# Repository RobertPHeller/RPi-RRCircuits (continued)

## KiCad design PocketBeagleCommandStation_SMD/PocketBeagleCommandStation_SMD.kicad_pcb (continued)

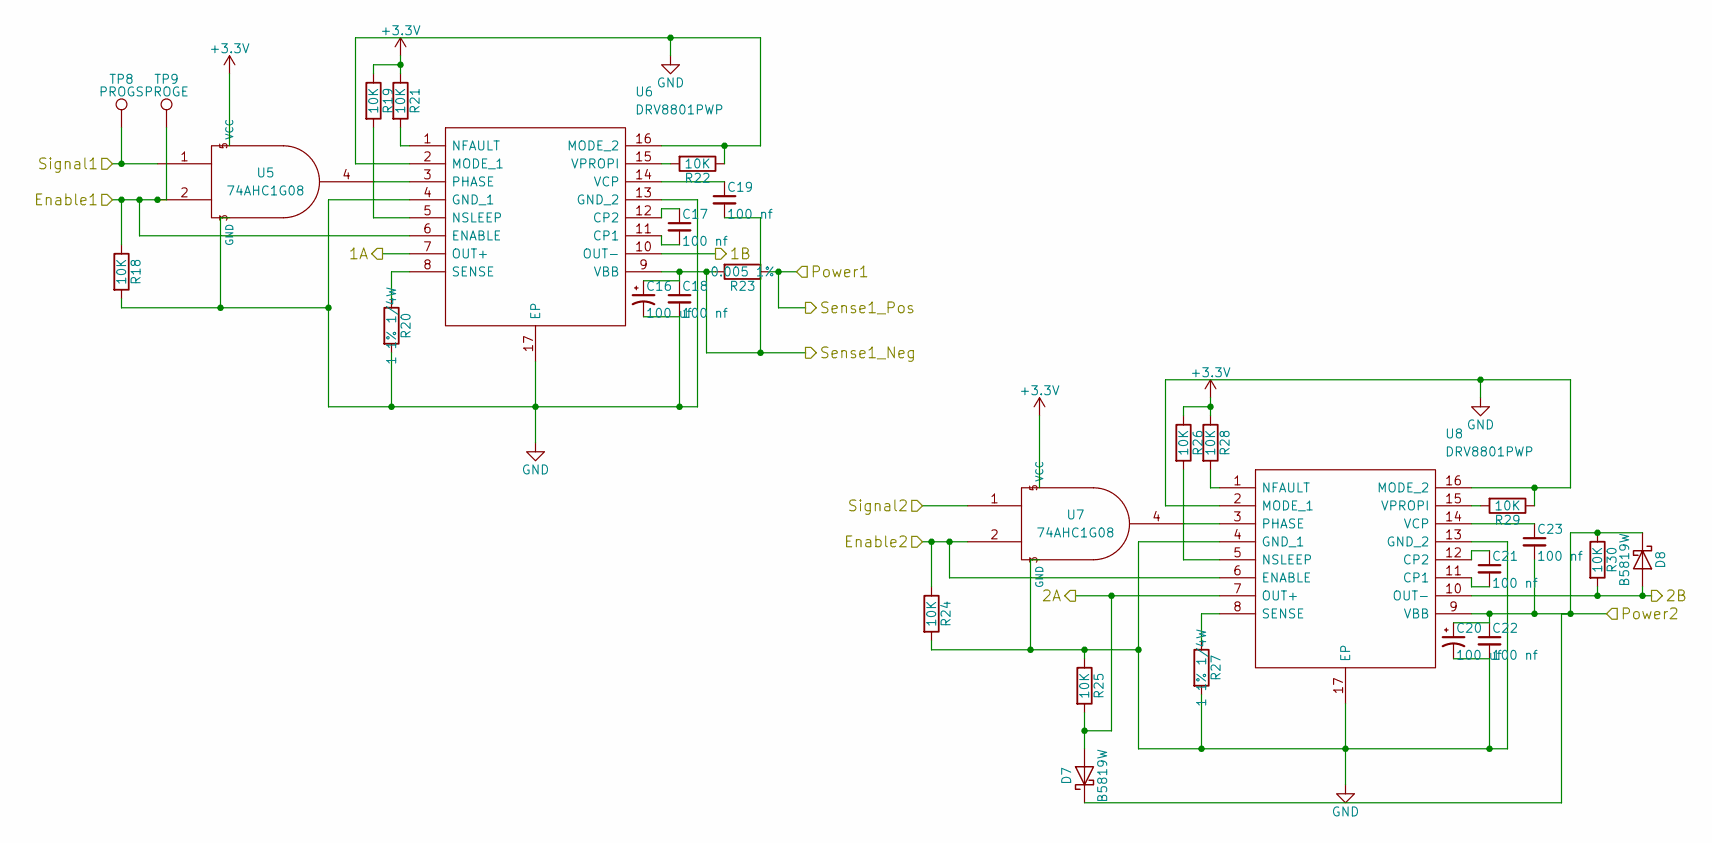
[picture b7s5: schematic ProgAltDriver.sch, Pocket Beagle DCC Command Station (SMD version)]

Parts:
C16, C20: 100 uf; CP_Elec_6.3x7.7; Mouser Part Number 710-865080545012
C17, C18, C19, C21, C22, C23: 100 nf; C_0603; Mouser Part Number 603-CC603KPX7R9BB104
D7, D8: B5819W; D_SOD-323; Mouser Part Number 833-B5819WS-TP
R18, R19, R21, R22, R24, R25, R26, R28, R29, R30: 10K; R_0603; Mouser Part Number 279-CRGCQ0603F10K
R20, R27: 1 1% 1/4W; R_1206; Mouser Part Number 71-CRCW1206-1-E3
R23: 0.005 1%; R_0612; Mouser Part Number 71-WSKW0612L5000FEA
TP8: PROGS; Measurement_Point_Round-SMD-Pad_Small
TP9: PROGE; Measurement_Point_Round-SMD-Pad_Small
U5, U7: 74AHC1G08; SOT-353_SC-70-5; Mouser Part Number 595-SN74AHC1G08DCRE4
U6, U8: DRV8801PWP; SOP65P640X120-17N; Mouser Part Number 595-DRV8801PWP

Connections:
+3V3: R19.1, R21.1, R26.1, R28.1, U5.5 (VCC), U7.5 (VCC); also elsewhere on the board
+12V: C20.1, C22.1, C23.2, D7.1 (K), D8.1 (K), R30.1, U8.9 (VBB); also elsewhere on the board
/OLBC_A: D7.2 (A), R25.2, U8.7 (OUT+); also elsewhere on the board
/OLBC_B: D8.2 (A), R30.2, U8.10 (OUT-); also elsewhere on the board
/OPS-ENABLE: R24.1, U7.2, U8.6 (ENABLE); also elsewhere on the board
/OPS-SIG: U7.1; also elsewhere on the board
/PROG-ENABLE: R18.1, TP9.1, U5.2, U6.6 (ENABLE); also elsewhere on the board
/PROG-SENSE-NEG: C16.1, C18.1, C19.2, R23.2, U6.9 (VBB); also elsewhere on the board
/PROG-SENSE-POS: R23.1; also elsewhere on the board
/PROG-SIG: TP8.1, U5.1; also elsewhere on the board
/Prog and LCC Alt H/L Driver/1A: U6.7 (OUT+); also elsewhere on the board
/Prog and LCC Alt H/L Driver/1B: U6.10 (OUT-); also elsewhere on the board
GND: C16.2, C18.2, C20.2, C22.2, R18.2, R20.2, R22.1, R24.2, R25.1, R27.2, R29.1, U5.3 (GND), U6.2 (MODE_1), U6.4 (GND_1), U6.13 (GND_2), U6.16 (MODE_2), U6.17 (EP), U7.3 (GND), U8.2 (MODE_1), U8.4 (GND_1), U8.13 (GND_2), U8.16 (MODE_2), U8.17 (EP); also elsewhere on the board
unnamed: C17.1, U6.12 (CP2)
unnamed: C17.2, U6.11 (CP1)
unnamed: C19.1, U6.14 (VCP)
unnamed: C21.1, U8.12 (CP2)
unnamed: C21.2, U8.11 (CP1)
unnamed: C23.1, U8.14 (VCP)
unnamed: R19.2, U6.5 (NSLEEP)
unnamed: R20.1, U6.8 (SENSE)
unnamed: R21.2, U6.1 (NFAULT)
unnamed: R22.2, U6.15 (VPROPI)
unnamed: R26.2, U8.5 (NSLEEP)
unnamed: R27.1, U8.8 (SENSE)
unnamed: R28.2, U8.1 (NFAULT)
unnamed: R29.2, U8.15 (VPROPI)
unnamed: U5.4, U6.3 (PHASE)
unnamed: U7.4, U8.3 (PHASE)

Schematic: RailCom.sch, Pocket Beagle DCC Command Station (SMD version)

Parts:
C24, C25, C26: 33 pf; C_0603; Mouser Part Number 187-CL10C330JB8NNNC
D10: B5819W; D_SOD-323; Mouser Part Number 833-B5819WS-TP
Q4, Q12: DMNH6022SSDQ; SOIC-8_3.9x4.9mm_Pitch1.27mm; Mouser Part Number 621-DMNH6022SSDQ-13
Q5, Q7, Q9, Q10: 2N7002; SOT-23; Mouser Part Number 512-2N7002
Q6, Q8, Q13, Q14: DTC143T; SOT-323_SC-70; Mouser Part Number 863-NSBC143TPDXV6T1G
R32, R34, R35, R36, R45: 10K; R_0603; Mouser Part Number 279-CRGCQ0603F10K
R33, R37: 2.4; R_1206; Mouser Part Number 71-CRCW12062R40FKEA
R38: 1.5K 1/4W; R_1206; Mouser Part Number 71-CRCW12061K50FKEAC
R39: 10K 1/4W; R_1206; Mouser Part Number 279-CRGCQ1206F10K
R40, R41, R42: 2.4K; R_0603; Mouser Part Number 667-ERJ-3EKF2401V
R43, R44, R46, R47: 24.9; R_1206; Mouser Part Number 652-CRT1206DY24R9ELF
U10: LMV339; TSSOP-14_4.4x5mm_Pitch0.65mm; Mouser Part Number 511-LMV339IPT

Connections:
+3V3: R34.1, R35.2, R41.1, R42.1, U10.3 (V+), U10.10 (-); also elsewhere on the board
/DCC_VS: R38.1, R39.1; also elsewhere on the board
/OLBC_A: Q12.7, Q12.8 (D); also elsewhere on the board
/OLBC_B: Q12.5 (D), Q12.6; also elsewhere on the board
/OPS_A: Q4.7, Q4.8 (D); also elsewhere on the board
/OPS_B: Q4.5 (D), Q4.6; also elsewhere on the board
/RAILCOM-DATA: D10.2 (A), R41.2, U10.2, U10.14; also elsewhere on the board
/RAILCOM-DIR: D10.1 (K), R42.2, U10.1; also elsewhere on the board
/RAILCOM-ENABLE: Q10.1 (G), R40.1; also elsewhere on the board
/RAILCOM-SHORT: Q6.3 (C), Q7.1 (G), Q8.3 (C), Q13.3 (C), Q14.3 (C), R35.1; also elsewhere on the board
/RAILCOM_OLBC_VREF: U10.9 (+); also elsewhere on the board
/RAILCOM_VREF: U10.5 (+), U10.7 (+); also elsewhere on the board
/Railcomm Interface/GATE-EN: Q4.2 (G), Q4.4 (G), Q5.3 (D), Q9.3 (D), Q12.2 (G), Q12.4 (G), R38.2
GND: C24.2, C25.2, C26.2, Q5.2 (S), Q6.2 (E), Q7.2 (S), Q8.2 (E), Q9.2 (S), Q10.2 (S), Q13.2 (E), Q14.2 (E), R33.1, R37.2, R40.2, R44.1, R46.2, U10.11 (+), U10.12 (V-); also elsewhere on the board
unnamed: C24.1, R32.1, U10.4 (-)
unnamed: C25.1, R36.1, U10.6 (-)
unnamed: C26.1, R45.1, U10.8 (-)
unnamed: Q4.1 (S), Q6.1 (B), R32.2, R33.2
unnamed: Q4.3 (S), Q8.1 (B), R36.2, R37.1
unnamed: Q5.1 (G), Q7.3 (D), R34.2
unnamed: Q9.1 (G), Q10.3 (D), R39.2
unnamed: Q12.1 (S), R43.2, R45.2
unnamed: Q12.3 (S), R47.1
unnamed: Q13.1 (B), R43.1, R44.2
unnamed: Q14.1 (B), R46.1, R47.2

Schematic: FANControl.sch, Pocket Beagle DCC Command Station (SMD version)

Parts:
C34: 100 uf; C_0603; Mouser Part Number 603-CC603KPX7R9BB104
D9: 1SS352H3F; D_SOD-323; Mouser Part Number 757-1SS352H3F
J6: - Fan +; TerminalBlock_Pheonix_MPT-2.54mm_2pol; Mouser Part Number 651-1725656
M1: Fan_IEC60617; 25mmFanMount; Mouser Part Number 490-CFM2510B1100-218
Q3: BSP52T3G; SOT-223; Mouser Part Number 863-BSP52T3G
R31: 1K; R_0603; Mouser Part Number 279-CRGCQ0603F1K0
U9: MCP9700T-E_LT; SOT65P210X110-5N; Mouser Part Number 579-MCP9700T-E/LT

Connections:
+3V3: C34.1, U9.4 (VDD); also elsewhere on the board
+12V: J6.1; also elsewhere on the board
/FAN-CONTROL: R31.2; also elsewhere on the board
/TEMP-SENSE: U9.3 (VOUT); also elsewhere on the board
GND: C34.2, D9.2 (A), Q3.3 (E), U9.2 (GND); also elsewhere on the board
unnamed: D9.1 (K), J6.2, Q3.2 (C), Q3.4 (C2)
unnamed: Q3.1 (B), R31.1

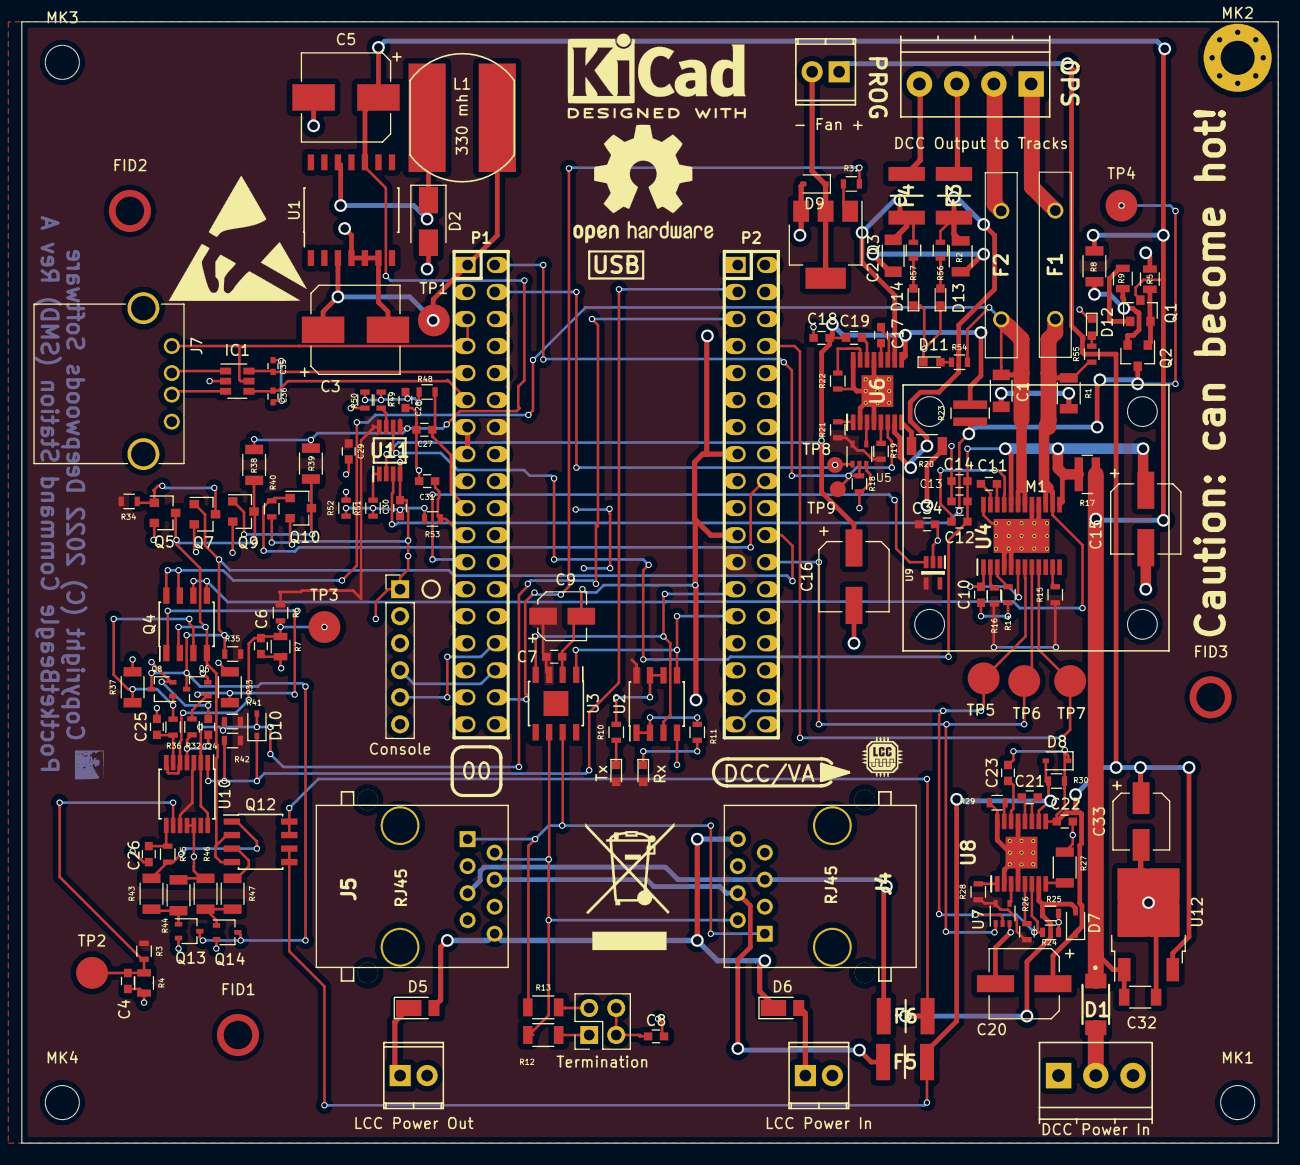
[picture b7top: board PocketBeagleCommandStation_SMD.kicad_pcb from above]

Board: 2 copper layers, 118.1 x 105.4 mm, 169 parts (0 on the bottom side), 108 nets.

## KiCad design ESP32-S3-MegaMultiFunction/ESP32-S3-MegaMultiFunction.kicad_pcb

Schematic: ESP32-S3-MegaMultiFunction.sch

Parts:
FD101, FD102, FD103: Fiduial; Fiducial_Modern_SilkscreenTop
J101: Conn_02x05_Odd_Even; IDC_Header_Straight_10pins
MK101, MK102, MK103, MK104: Mounting_Hole; MountingHole_3.5mm

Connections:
/Line1: J101.10; also elsewhere on the board
/Line2: J101.9; also elsewhere on the board
/Line3: J101.8; also elsewhere on the board
/Line4: J101.7; also elsewhere on the board
/Line5: J101.4; also elsewhere on the board
/Line6: J101.3; also elsewhere on the board
/Line7: J101.2; also elsewhere on the board
/Line8: J101.1; also elsewhere on the board
GND: J101.5; also elsewhere on the board

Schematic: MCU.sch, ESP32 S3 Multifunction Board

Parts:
C201, C202: 10uf; C_0805; Mouser Part Number 187-CL21A106MQFNNNE
C203, C208, C210, C217: 1uf; C_0402; Mouser Part Number 80-C0402C101K8RAUTO
C204, C205, C206, C207, C211, C212: 100nf; C_0402; Mouser Part Number 710-885012105001
C209: 100pf; C_0402; Mouser Part Number 80-C0402C101K3RAUTO
C213, C214, C215, C216: 22pf; C_0402; Mouser Part Number 187-CL05C220JB5NNND
D201: ACT1; LED_0402; Mouser Part Number 710-150040GS73220
D202: ACT2; LED_0402; Mouser Part Number 710-150040SS73220
IC201: ESP32-S3FN8; QFN-56-1EP_7x7mm_Pitch0.4mm; Manufacturer_Part_Number ESP32-S3FN8; Mouser Part Number 356-ESP32-S3FN8
IC202: USBLC6-2SC6; SOT-23-6; Mouser Part Number 511-USBLC6-2SC6
J201: USB_OTG; GCT_USB4105-GF-A; Mouser Part Number 640-USB4105-GF-A-120
L201: 2.0nH; L_0402; Mouser Part Number 810-MLG1005S2N0ST000
R201, R202, R203, R204, R210, R211: 10K; R_0402; Mouser Part Number 603-RC0402JR-1310KL
R205, R207: 2.4K; R_0402; Mouser Part Number 71-CRCW06032K40JNEAC
R206, R208: 270; R_0402; Mouser Part Number 754-RR0510P-271D
R209: 0; R_0402; Mouser Part Number 71-CRCW04020000Z0EDC
R212, R213: 5.1K; R_0402
SW201: RESET; SW_SPST_B3U-1000P-B; Mouser Part Number 653-B3U-1000P-B
SW202: BOOT; SW_SPST_B3U-1000P-B; Mouser Part Number 653-B3U-1000P-B
U201, U202, U203: MCP23017; SOIC-28W_7.5x17.9mm_Pitch1.27mm
Y201: 40 Mhz; FA20_H; Mouser Part Number 732-FA-20H40MF10Z-W3

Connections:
/Buttons/Button1: U203.21 (GPA0); also elsewhere on the board
/Buttons/Button2: U203.22 (GPA1); also elsewhere on the board
/Buttons/Button3: U203.23 (GPA2); also elsewhere on the board
/Buttons/Button4: U203.24 (GPA3); also elsewhere on the board
/Buttons/Button5: U203.25 (GPA4); also elsewhere on the board
/Buttons/Button6: U203.26 (GPA5); also elsewhere on the board
/Buttons/Button7: U203.27 (GPA6); also elsewhere on the board
/Buttons/Button8: U203.28 (GPA7); also elsewhere on the board
/CAN Transciver/CAN_RX: IC201.9 (GPIO4); also elsewhere on the board
/CAN Transciver/CAN_TX: IC201.10 (GPIO5); also elsewhere on the board
/LED/Drivers/LED1: U201.1 (GPB0); also elsewhere on the board
/LED/Drivers/LED2: U201.2 (GPB1); also elsewhere on the board
/LED/Drivers/LED3: U201.3 (GPB2); also elsewhere on the board
/LED/Drivers/LED4: U201.4 (GPB3); also elsewhere on the board
/LED/Drivers/LED5: U201.5 (GPB4); also elsewhere on the board
/LED/Drivers/LED6: U201.6 (GPB5); also elsewhere on the board
/LED/Drivers/LED7: U201.7 (GPB6); also elsewhere on the board
/LED/Drivers/LED8: U201.8 (GPB7); also elsewhere on the board
/Line1: U203.1 (GPB0); also elsewhere on the board
/Line2: U203.2 (GPB1); also elsewhere on the board
/Line3: U203.3 (GPB2); also elsewhere on the board
/Line4: U203.4 (GPB3); also elsewhere on the board
/Line5: U203.5 (GPB4); also elsewhere on the board
/Line6: U203.6 (GPB5); also elsewhere on the board
/Line7: U203.7 (GPB6); also elsewhere on the board
/Line8: U203.8 (GPB7); also elsewhere on the board
/MCU/D+: C216.1, IC201.26 (GPIO20), IC202.1 (I/O1_1)
/MCU/D-: C215.2, IC201.25 (GPIO19), IC202.3 (I/O2_1)
/MCU/GPIO0(Act2): D202.1 (K), IC201.5 (GPIO0), SW202.2
/MCU/GPIO15(Act1): D201.1 (K), IC201.21 (XTAL_32K_P)
/MCU/Motor1: U202.21 (GPA0); also elsewhere on the board
/MCU/Motor2: U202.22 (GPA1); also elsewhere on the board
/MCU/Motor3: U202.23 (GPA2); also elsewhere on the board
/MCU/Motor4: U202.24 (GPA3); also elsewhere on the board
/MCU/Motor5: U202.25 (GPA4); also elsewhere on the board
/MCU/Motor6: U202.26 (GPA5); also elsewhere on the board
/MCU/Motor7: U202.27 (GPA6); also elsewhere on the board
/MCU/Motor8: U202.28 (GPA7); also elsewhere on the board
/MCU/OD1: U201.21 (GPA0); also elsewhere on the board
/MCU/OD2: U201.22 (GPA1); also elsewhere on the board
/MCU/OD3: U201.23 (GPA2); also elsewhere on the board
/MCU/OD4: U201.24 (GPA3); also elsewhere on the board
/MCU/OD5: U201.25 (GPA4); also elsewhere on the board
/MCU/OD6: U201.26 (GPA5); also elsewhere on the board
/MCU/OD7: U201.27 (GPA6); also elsewhere on the board
/MCU/OD8: U201.28 (GPA7); also elsewhere on the board
/MCU/Points1: U202.1 (GPB0); also elsewhere on the board
/MCU/Points2: U202.2 (GPB1); also elsewhere on the board
/MCU/Points3: U202.3 (GPB2); also elsewhere on the board
/MCU/Points4: U202.4 (GPB3); also elsewhere on the board
/MCU/Points5: U202.5 (GPB4); also elsewhere on the board
/MCU/Points6: U202.6 (GPB5); also elsewhere on the board
/MCU/Points7: U202.7 (GPB6); also elsewhere on the board
/MCU/Points8: U202.8 (GPB7); also elsewhere on the board
/MCU/RESET: C210.1, IC201.4 (CHIP_PU), R204.2, SW201.2
/MCU/SCL: IC201.8 (GPIO3), R205.1, U201.12 (SCL), U202.12 (SCL), U203.12 (SCL); also elsewhere on the board
/MCU/SDA: IC201.7 (GPIO2), R207.2, U201.13 (SDA), U202.13 (SDA), U203.13 (SDA); also elsewhere on the board
/MCU/VDD3P3: C201.1, C202.1, C203.1, C205.1, IC201.2 (VDD3P3_1), IC201.3 (VDD3P3_2), L201.2
GND: C201.2, C202.2, C203.2, C204.2, C205.2, C206.2, C207.2, C208.2, C209.2, C210.2, C211.2, C212.2, C213.1, C214.1, C215.1, C216.2, C217.2, IC201.57 (EP), IC202.2 (GND), J201.A1/B (GND), J201.B1/A (GND), J201.G1 (SHIELD), J201.G2 (SHIELD), J201.G3 (SHIELD), J201.G4 (SHIELD), R212.2, R213.2, SW201.1, SW202.1, U201.10 (GND), U201.16 (A1), U201.17 (A2), U202.10 (GND), U202.15 (A0), U202.16 (A1), U202.17 (A2), U203.10 (GND), U203.15 (A0), U203.17 (A2), Y201.2, Y201.4; also elsewhere on the board
unnamed: C213.2, R209.1, Y201.3
unnamed: C214.2, IC201.53 (XTAL_N), Y201.1
unnamed: C217.1, IC201.29 (VDD_SPI)
unnamed: D201.2 (A), R206.2
unnamed: D202.2 (A), R208.2
unnamed: IC201.54 (XTAL_P), R209.2
unnamed: IC202.4 (I/O2_2), J201.A7 (D-), J201.B7 (D-)
unnamed: IC202.6 (I/O1_2), J201.A6 (D+), J201.B6 (D+)
unnamed: J201.A5 (CC1), R213.1
unnamed: J201.B5 (CC2), R212.1
unnamed: R201.2, U201.18 (~RESET)
unnamed: R202.2, U201.15 (A0)
unnamed: R203.2, U202.18 (~RESET)
unnamed: R210.2, U203.18 (~RESET)
unnamed: R211.2, U203.16 (A1)
VBUS: IC202.5 (VBUS), J201.A4/B (VBUS), J201.B4/A (VBUS); also elsewhere on the board

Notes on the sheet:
Pins 2,3
Pin 46
Pins 55, 56
Pin 20
One for each MCP23017

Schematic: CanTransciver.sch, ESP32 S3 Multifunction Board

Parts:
C301: .1 uf; C_0603; Mouser Part Number 710-885012206095
C302: 15 uf 15V; CP_Elec_4x5.7; Mouser Part Number 647-UUD1C150MCL
C303: 47 nf; C_0603; Mouser Part Number 710-885012206093
D301, D302: DFLS240-7; D_PowerDI-123; Mouser Part Number 621-DFLS240-7
J301, J302: RJ45; RJ45_8N-S; Mouser Part Number 710-615008144221
JP301: Termination; Pin_Header_Straight_2x02_Pitch2.54mm; Mouser Part Number 649-67997-404HLF
R301, R302: 60 Ohms; R_1206; Mouser Part Number 71-CRCW120660R0KNAIF
T301: - 15 in +; TerminalBlock_Pheonix_MPT-2.54mm_2pol; Mouser Part Number 651-1725656
T302: - 15 out +; TerminalBlock_Pheonix_MPT-2.54mm_2pol; Mouser Part Number 651-1725656
U301: TCAN332DR; SOIC-8_3.9x4.9mm_Pitch1.27mm; Mouser Part Number 595-TCAN332DR

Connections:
/CAN Transciver/CANH: J301.1, J302.1, R301.1, U301.7 (CANH)
/CAN Transciver/CANL: J301.2, J302.2, R302.1, U301.6 (CANL)
/CAN Transciver/CAN_RX: U301.4 (R); also elsewhere on the board
/CAN Transciver/CAN_TX: U301.1 (D); also elsewhere on the board
CAN +12V: D301.1 (K), D302.2 (A), J301.8, J302.8; also elsewhere on the board
GND: C301.2, C302.2, C303.2, J301.3, J301.6, J301.7, J302.3, J302.6, J302.7, T301.2, T302.2, U301.2 (GND); also elsewhere on the board
unnamed: C303.1, JP301.3, JP301.4
unnamed: D301.2 (A), T301.1
unnamed: D302.1 (K), T302.1
unnamed: J301.4, J302.4
unnamed: J301.5, J302.5
unnamed: JP301.1, R301.2
unnamed: JP301.2, R302.2

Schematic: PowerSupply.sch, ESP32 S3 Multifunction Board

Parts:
C401: 220 uf 25V; CP_Elec_8x10; Mouser Part Number 647-UWT1E221MNL1GS
C402: 22 uf 100V; CP_Elec_8x10; Mouser Part Number 647-UUX2A220MNL6GS
D401: CMSH1-60 TR13; D_SMB; Mouser Part Number 610-CMSH1-60TR13
D402, D403: DFLS240-7; D_PowerDI-123; Mouser Part Number 621-DFLS240-7
L401: 330 uh; SRN1060; Mouser Part Number 652-SRN1060-331M
U401: LM2574N-3.3; SOIC-14_7.4x8.7mm_Pitch1.27mm; Mouser Part Number 926-LM2574MX33NOPB

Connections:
CAN +12V: D402.2 (A); also elsewhere on the board
GND: C401.2, C402.2, D401.2 (A), U401.4 (SigGnd), U401.5 (Oh/Off), U401.6 (PwrGnd); also elsewhere on the board
unnamed: C402.1, D402.1 (K), D403.1 (K), U401.10 (Vin)
unnamed: D401.1 (K), L401.1, U401.12 (Out)
VBUS: D403.2 (A); also elsewhere on the board

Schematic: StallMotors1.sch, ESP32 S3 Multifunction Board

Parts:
C501, C502: .1 uf; C_0603; Mouser Part Number 710-885012206095
D501: DFLS240-7; D_PowerDI-123; Mouser Part Number 621-DFLS240-7
J501: -SM+; TerminalBlock_Pheonix_MPT-2.54mm_2pol; Mouser Part Number 651-172565
J502: Motor 1; 474817; Mouser Part Number 305-474817
J503: Motor 2; 474817; Mouser Part Number 305-474817
J504: Motor 3; 474817; Mouser Part Number 305-474817
J505: Motor 4; 474817; Mouser Part Number 305-474817
RR501: 10K Ohms; 4814P; Mouser Part Number 652-4814P-2LF-10K
U501, U502: 74HCT00; SOIC-14_3.9x8.7mm_Pitch1.27mm; Mouser Part Number 595-SN74AHC00D
U503, U504, U505, U506: TC4428; SOIC-8_3.9x4.9mm_Pitch1.27mm; Mouser Part Number 579-TC4428VOA

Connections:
/MCU/Motor1: U503.2 (IN), U503.4 (IN); also elsewhere on the board
/MCU/Motor2: U504.2 (IN), U504.4 (IN); also elsewhere on the board
/MCU/Motor3: U505.2 (IN), U505.4 (IN); also elsewhere on the board
/MCU/Motor4: U506.2 (IN), U506.4 (IN); also elsewhere on the board
/MCU/Points1: U501.3, U501.4; also elsewhere on the board
/MCU/Points2: U501.8, U501.12; also elsewhere on the board
/MCU/Points3: U502.3, U502.4; also elsewhere on the board
/MCU/Points4: U502.8, U502.12; also elsewhere on the board
/Stall Motors 1/M1A: J502.1, U503.5 (Out)
/Stall Motors 1/M1B: J502.2, U503.7 (Out)
/Stall Motors 1/M2A: J503.1, U504.5 (Out)
/Stall Motors 1/M2B: J503.2, U504.7 (Out)
/Stall Motors 1/M3A: J504.1, U505.5 (Out)
/Stall Motors 1/M3B: J504.2, U505.7 (Out)
/Stall Motors 1/M4A: J505.1, U506.5 (Out)
/Stall Motors 1/M4B: J505.2, U506.7 (Out)
/Stall Motors 1/P1A: J502.3, RR501.6 (R6), U501.1
/Stall Motors 1/P1B: J502.5, RR501.5 (R5), U501.5
/Stall Motors 1/P2A: J503.3, RR501.4 (R4), U501.9
/Stall Motors 1/P2B: J503.5, RR501.3 (R3), U501.13
/Stall Motors 1/P3A: J504.3, RR501.13 (R13), U502.1
/Stall Motors 1/P3B: J504.5, RR501.12 (R12), U502.5
/Stall Motors 1/P4A: J505.3, RR501.11 (R11), U502.9
/Stall Motors 1/P4B: J505.5, RR501.10 (R10), U502.13
CAN +12V: D501.2 (A); also elsewhere on the board
GND: C501.2, C502.2, J501.2, J502.4, J503.4, J504.4, J505.4, U501.7 (GND), U502.7 (GND), U503.3 (GND), U504.3 (GND), U505.3 (GND), U506.3 (GND); also elsewhere on the board
unnamed: U501.2, U501.6
unnamed: U501.10, U501.11
unnamed: U502.2, U502.6
unnamed: U502.10, U502.11
SMPower: D501.1 (K), J501.1, U503.6 (Vdd), U504.6 (Vdd), U505.6 (Vdd), U506.6 (Vdd); also elsewhere on the board

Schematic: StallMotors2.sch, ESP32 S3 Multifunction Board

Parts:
C601, C602: .1 uf; C_0603; Mouser Part Number 710-885012206095
J601: Motor 5; 474817; Mouser Part Number 305-474817
J602: Motor 6; 474817; Mouser Part Number 305-474817
J603: Motor 7; 474817; Mouser Part Number 305-474817
J604: Motor 8; 474817; Mouser Part Number 305-474817
RR601: 10K Ohms; 4814P; Mouser Part Number 652-4814P-2LF-10K
U601, U602: 74HCT00; SOIC-14_3.9x8.7mm_Pitch1.27mm; Mouser Part Number 595-SN74AHC00D
U603, U604, U605, U606: TC4428; SOIC-8_3.9x4.9mm_Pitch1.27mm; Mouser Part Number 579-TC4428VOA

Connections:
/MCU/Motor5: U603.2 (IN), U603.4 (IN); also elsewhere on the board
/MCU/Motor6: U604.2 (IN), U604.4 (IN); also elsewhere on the board
/MCU/Motor7: U605.2 (IN), U605.4 (IN); also elsewhere on the board
/MCU/Motor8: U606.2 (IN), U606.4 (IN); also elsewhere on the board
/MCU/Points5: U601.3, U601.4; also elsewhere on the board
/MCU/Points6: U601.8, U601.12; also elsewhere on the board
/MCU/Points7: U602.3, U602.4; also elsewhere on the board
/MCU/Points8: U602.8, U602.12; also elsewhere on the board
/Stall Motors 2/M5A: J601.1, U603.5 (Out)
/Stall Motors 2/M5B: J601.2, U603.7 (Out)
/Stall Motors 2/M6A: J602.1, U604.5 (Out)
/Stall Motors 2/M6B: J602.2, U604.7 (Out)
/Stall Motors 2/M7A: J603.1, U605.5 (Out)
/Stall Motors 2/M7B: J603.2, U605.7 (Out)
/Stall Motors 2/M8A: J604.1, U606.5 (Out)
/Stall Motors 2/M8B: J604.2, U606.7 (Out)
/Stall Motors 2/P5A: J601.3, RR601.6 (R6), U601.1
/Stall Motors 2/P5B: J601.5, RR601.5 (R5), U601.5
/Stall Motors 2/P6A: J602.3, RR601.4 (R4), U601.9
/Stall Motors 2/P6B: J602.5, RR601.3 (R3), U601.13
/Stall Motors 2/P7A: J603.3, RR601.13 (R13), U602.1
/Stall Motors 2/P7B: J603.5, RR601.12 (R12), U602.5
/Stall Motors 2/P8A: J604.3, RR601.11 (R11), U602.9
/Stall Motors 2/P8B: J604.5, RR601.10 (R10), U602.13
GND: C601.2, C602.2, J601.4, J602.4, J603.4, J604.4, U601.7 (GND), U602.7 (GND), U603.3 (GND), U604.3 (GND), U605.3 (GND), U606.3 (GND); also elsewhere on the board
unnamed: U601.2, U601.6
unnamed: U601.10, U601.11
unnamed: U602.2, U602.6
unnamed: U602.10, U602.11
SMPower: U603.6 (Vdd), U604.6 (Vdd), U605.6 (Vdd), U606.6 (Vdd); also elsewhere on the board

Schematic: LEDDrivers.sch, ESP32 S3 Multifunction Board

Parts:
R701, R703, R705, R707, R709, R711, R713, R715: R; R_Axial_DIN0207_L6.3mm_D2.5mm_P7.62mm_Horizontal
R702, R704, R706, R708, R710, R712, R714, R716: 1.5K Ohms; R_0603; Mouser Part Number 71-CRCW06031K50JNEAC
Term701: + 1 2 3 4 5 6 7 8 GND; TerminalBlock_Pheonix_MPT-2.54mm_10pol; Mouser Part Number 651-1725737
U701, U702, U703, U704: TC4426; SOIC-8_3.9x4.9mm_Pitch1.27mm; Mouser Part Number 579-TC1426COA713

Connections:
/LED/Drivers/LED1: U701.4 (IN); also elsewhere on the board
/LED/Drivers/LED2: U701.2 (IN); also elsewhere on the board
/LED/Drivers/LED3: U702.4 (IN); also elsewhere on the board
/LED/Drivers/LED4: U702.2 (IN); also elsewhere on the board
/LED/Drivers/LED5: U703.4 (IN); also elsewhere on the board
/LED/Drivers/LED6: U703.2 (IN); also elsewhere on the board
/LED/Drivers/LED7: U704.4 (IN); also elsewhere on the board
/LED/Drivers/LED8: U704.2 (IN); also elsewhere on the board
GND: Term701.10, U701.3 (GND), U702.3 (GND), U703.3 (GND), U704.3 (GND); also elsewhere on the board
unnamed: R701.1, R702.1, Term701.2
unnamed: R701.2, R702.2, U701.5 (Out)
unnamed: R703.1, R704.1, Term701.3
unnamed: R703.2, R704.2, U701.7 (Out)
unnamed: R705.1, R706.1, Term701.4
unnamed: R705.2, R706.2, U702.5 (Out)
unnamed: R707.1, R708.1, Term701.5
unnamed: R707.2, R708.2, U702.7 (Out)
unnamed: R709.1, R710.1, Term701.6
unnamed: R709.2, R710.2, U703.5 (Out)
unnamed: R711.1, R712.1, Term701.7
unnamed: R711.2, R712.2, U703.7 (Out)
unnamed: R713.1, R714.1, Term701.8
unnamed: R713.2, R714.2, U704.5 (Out)
unnamed: R715.1, R716.1, Term701.9
unnamed: R715.2, R716.2, U704.7 (Out)
VPower: Term701.1, U701.6 (VPower), U702.6 (VPower), U703.6 (VPower), U704.6 (VPower)

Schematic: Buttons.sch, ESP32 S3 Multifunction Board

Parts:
C801, C806: .1 uf; C_0603; Mouser Part Number 710-885012206095
C802, C803, C804, C805, C807, C808, C809, C810: 10 nf; C_0603; Mouser Part Number 710-885382206002
R801, R802, R803, R804, R805, R806, R807, R808: 10K Ohms; R_0603; Mouser Part Number 71-CRCW060310K0JNEBC
Term801: GND 8 7 6 5 4 3 2 1; TerminalBlock_Pheonix_MPT-2.54mm_9pol; Mouser Part Number 651-1725724
U801: 74HCT14; SOIC-14_3.9x8.7mm_Pitch1.27mm
U802: 74HCT14; SOIC-14_3.9x8.7mm_Pitch1.27mm; Mouser Part Number 595-CD74HC14M

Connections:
/Buttons/Button1: U802.6; also elsewhere on the board
/Buttons/Button2: U802.8; also elsewhere on the board
/Buttons/Button3: U802.10; also elsewhere on the board
/Buttons/Button4: U802.12; also elsewhere on the board
/Buttons/Button5: U801.6; also elsewhere on the board
/Buttons/Button6: U801.8; also elsewhere on the board
/Buttons/Button7: U801.10; also elsewhere on the board
/Buttons/Button8: U801.12; also elsewhere on the board
GND: C801.2, C802.2, C803.2, C804.2, C805.2, C806.2, C807.2, C808.2, C809.2, C810.2, Term801.9, U801.1, U801.3, U801.7 (GND), U802.1, U802.3, U802.7 (GND); also elsewhere on the board
unnamed: C802.1, R801.2, Term801.7, U801.11
unnamed: C803.1, R802.2, Term801.8, U801.13
unnamed: C804.1, R803.2, Term801.5, U801.5
unnamed: C805.1, R804.2, Term801.6, U801.9
unnamed: C807.1, R805.2, Term801.1, U802.5
unnamed: C808.1, R806.2, Term801.2, U802.9
unnamed: C809.1, R807.2, Term801.4, U802.13
unnamed: C810.1, R808.2, Term801.3, U802.11

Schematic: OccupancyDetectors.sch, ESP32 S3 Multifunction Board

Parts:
C901, C902, C903, C904, C905, C906, C907, C908: 2.2uf 50V; CP_Elec_4x5.7; Mouser Part Number 710-865080140002
D901, D902, D903, D904, D905, D906, D907, D908, D913, D914, D915, D916, D917, D918, D919, D920: 1N4148; D_SOD-323; Mouser Part Number 750-1N4148WS-HF
D909, D910, D911, D912, D921, D922, D923, D924: LED; LED_0603; Mouser Part Number 710-150060SS55040
J901: OC 1-4; 474818; Mouser Part Number 305-474818
J902: OC 5-8; 474818; Mouser Part Number 305-474818
R901, R902, R903, R904, R913, R914, R915, R916: 22K Ohms; R_0603; Mouser Part Number 71-RCG060322K0JNEA
R905, R906, R907, R908, R917, R918, R919, R920: 1M Ohms; R_0603; Mouser Part Number 71-CRCW06031M00JNEAC
R909, R910, R911, R912, R921, R922, R923, R924: 2.7K Ohms; R_0603; Mouser Part Number 71-CRCW06032K70JNEAC
RV901, RV902, RV903, RV904, RV905, RV906, RV907, RV908: 25K Ohms; Potentiometer_Trimmer_Bourns_3214J; Mouser Part Number 652-3314J-1-253E
U901, U903: LM339; SOIC-14_3.9x8.7mm_Pitch1.27mm; Mouser Part Number 595-LM339DR
U902, U904: LM339; SOIC-14_3.9x8.7mm_Pitch1.27mm

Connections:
/MCU/OD1: D909.1 (K), U901.1; also elsewhere on the board
/MCU/OD2: D910.1 (K), U901.14; also elsewhere on the board
/MCU/OD3: D911.1 (K), U902.1; also elsewhere on the board
/MCU/OD4: D912.1 (K), U902.14; also elsewhere on the board
/MCU/OD5: D921.1 (K), U903.1; also elsewhere on the board
/MCU/OD6: D922.1 (K), U903.14; also elsewhere on the board
/MCU/OD7: D923.1 (K), U904.1; also elsewhere on the board
/MCU/OD8: D924.1 (K), U904.14; also elsewhere on the board
GND: C901.2, C902.2, C903.2, C904.2, C905.2, C906.2, C907.2, C908.2, RV901.1, RV902.1, RV903.1, RV904.1, RV905.1, RV906.1, RV907.1, RV908.1, U901.12 (V-), U902.12 (V-), U903.12 (V-), U904.12 (V-); also elsewhere on the board
unnamed: C901.1, R905.2, U901.2, U901.7 (+)
unnamed: C902.1, R906.2, U901.9 (+), U901.13
unnamed: C903.1, R907.2, U902.2, U902.7 (+)
unnamed: C904.1, R908.2, U902.9 (+), U902.13
unnamed: C905.1, R917.2, U903.2, U903.7 (+)
unnamed: C906.1, R918.2, U903.9 (+), U903.13
unnamed: C907.1, R919.2, U904.2, U904.7 (+)
unnamed: C908.1, R920.2, U904.9 (+), U904.13
unnamed: D901.1 (K), D905.2 (A), J901.8, U901.4 (-)
unnamed: D901.2 (A), D905.1 (K), J901.7, RV901.2
unnamed: D902.1 (K), D906.2 (A), J901.6, U901.10 (-)
unnamed: D902.2 (A), D906.1 (K), J901.5, RV902.2
unnamed: D903.1 (K), D907.2 (A), J901.4, U902.4 (-)
unnamed: D903.2 (A), D907.1 (K), J901.3, RV903.2
unnamed: D904.1 (K), D908.2 (A), J901.2, U902.10 (-)
unnamed: D904.2 (A), D908.1 (K), J901.1, RV904.2
unnamed: D909.2 (A), R909.2
unnamed: D910.2 (A), R910.2
unnamed: D911.2 (A), R911.2
unnamed: D912.2 (A), R912.2
unnamed: D913.1 (K), D917.2 (A), J902.8, U903.4 (-)
unnamed: D913.2 (A), D917.1 (K), J902.7, RV905.2
unnamed: D914.1 (K), D918.2 (A), J902.6, U903.10 (-)
unnamed: D914.2 (A), D918.1 (K), J902.5, RV906.2
unnamed: D915.1 (K), D919.2 (A), J902.4, U904.4 (-)
unnamed: D915.2 (A), D919.1 (K), J902.3, RV907.2
unnamed: D916.1 (K), D920.2 (A), J902.2, U904.10 (-)
unnamed: D916.2 (A), D920.1 (K), J902.1, RV908.2
unnamed: D921.2 (A), R921.2
unnamed: D922.2 (A), R922.2
unnamed: D923.2 (A), R923.2
unnamed: D924.2 (A), R924.2
unnamed: R901.2, RV901.3, U901.5 (+), U901.6 (-)
unnamed: R902.2, RV902.3, U901.8 (-), U901.11 (+)
unnamed: R903.2, RV903.3, U902.5 (+), U902.6 (-)
unnamed: R904.2, RV904.3, U902.8 (-), U902.11 (+)
unnamed: R913.2, RV905.3, U903.5 (+), U903.6 (-)
unnamed: R914.2, RV906.3, U903.8 (-), U903.11 (+)
unnamed: R915.2, RV907.3, U904.5 (+), U904.6 (-)
unnamed: R916.2, RV908.3, U904.8 (-), U904.11 (+)

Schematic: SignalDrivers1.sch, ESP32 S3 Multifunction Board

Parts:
C1001: .1 uf; C_0603; Mouser Part Number 710-885012206095
D1001: DFLS240-7; D_PowerDI-123; Mouser Part Number 621-DFLS240-7
JP1001, JP1002, JP1003, JP1004, JP1005, JP1006, JP1007, JP1008: 0; R_1206; Mouser Part Number 71-CRCW12060000Z0EBC
P1001: A7 A6 A5 A4 A3 A2 A1 A0 C; TerminalBlock_Pheonix_MPT-2.54mm_9pol; Mouser Part Number 651-1725724
P1002: B7 B6 B5 B4 B3 B2 B1 B0 C; TerminalBlock_Pheonix_MPT-2.54mm_9pol; Mouser Part Number 651-1725724
RP1001, RP1002: 1.5K Ohms; 4816P; Mouser Part Number 652-4816P-T1LF-1.5K
T1001: + 12V -; TerminalBlock_Pheonix_MPT-2.54mm_2pol; Mouser Part Number 651-1725656
U1001: PCA9685; TSSOP-28_4.4x9.7mm_Pitch0.65mm; Mouser Part Number 771-PCA9685PW,118
U1002, U1003: TBD62X83A; SOIC-18W_7.5x11.6mm_Pitch1.27mm; Mouser Part Number 757-TBD62083AFG or 757-TBD62783AFG

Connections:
+12V: D1001.1 (K), JP1001.2, JP1004.1, JP1005.2, JP1008.1, T1001.1; also elsewhere on the board
/MCU/SCL: U1001.26 (SCL); also elsewhere on the board
/MCU/SDA: U1001.27 (SDA); also elsewhere on the board
CAN +12V: D1001.2 (A); also elsewhere on the board
GND: C1001.2, JP1002.2, JP1003.1, JP1006.2, JP1007.1, T1001.2, U1001.1 (A0), U1001.2 (A1), U1001.3 (A2), U1001.4 (A3), U1001.5 (A4), U1001.14 (Vss), U1001.23 (OE), U1001.24 (A5), U1001.25 (ExtCLK); also elsewhere on the board
unnamed: JP1001.1, JP1003.2, P1001.9, U1002.10 (OC)
unnamed: JP1002.1, JP1004.2, U1002.9 (IC)
unnamed: JP1005.1, JP1007.2, P1002.9, U1003.10 (OC)
unnamed: JP1006.1, JP1008.2, U1003.9 (IC)
unnamed: P1001.1, RP1001.16 (R1.2)
unnamed: P1001.2, RP1001.15 (R2.2)
unnamed: P1001.3, RP1001.14 (R3.2)
unnamed: P1001.4, RP1001.13 (R4.2)
unnamed: P1001.5, RP1001.12 (R5.2)
unnamed: P1001.6, RP1001.11 (R6.2)
unnamed: P1001.7, RP1001.10 (R7.2)
unnamed: P1001.8, RP1001.9 (R8.2)
unnamed: P1002.1, RP1002.16 (R1.2)
unnamed: P1002.2, RP1002.15 (R2.2)
unnamed: P1002.3, RP1002.14 (R3.2)
unnamed: P1002.4, RP1002.13 (R4.2)
unnamed: P1002.5, RP1002.12 (R5.2)
unnamed: P1002.6, RP1002.11 (R6.2)
unnamed: P1002.7, RP1002.10 (R7.2)
unnamed: P1002.8, RP1002.9 (R8.2)
unnamed: RP1001.1 (R1.1), U1002.18 (Out)
unnamed: RP1001.2 (R2.1), U1002.17 (Out)
unnamed: RP1001.3 (R3.1), U1002.16 (Out)
unnamed: RP1001.4 (R4.1), U1002.15 (Out)
unnamed: RP1001.5 (R5.1), U1002.14 (Out)
unnamed: RP1001.6 (R6.1), U1002.13 (Out)
unnamed: RP1001.7 (R7.1), U1002.12 (Out)
unnamed: RP1001.8 (R8.1), U1002.11 (Out)
unnamed: RP1002.1 (R1.1), U1003.18 (Out)
unnamed: RP1002.2 (R2.1), U1003.17 (Out)
unnamed: RP1002.3 (R3.1), U1003.16 (Out)
unnamed: RP1002.4 (R4.1), U1003.15 (Out)
unnamed: RP1002.5 (R5.1), U1003.14 (Out)
unnamed: RP1002.6 (R6.1), U1003.13 (Out)
unnamed: RP1002.7 (R7.1), U1003.12 (Out)
unnamed: RP1002.8 (R8.1), U1003.11 (Out)
unnamed: U1001.6 (LED0), U1002.8 (In)
unnamed: U1001.7 (LED1), U1002.7 (In)
unnamed: U1001.8 (LED2), U1002.6 (In)
unnamed: U1001.9 (LED3), U1002.5 (In)
unnamed: U1001.10 (LED4), U1002.4 (In)
unnamed: U1001.11 (LED5), U1002.3 (In)
unnamed: U1001.12 (LED6), U1002.2 (In)
unnamed: U1001.13 (LED7), U1002.1 (In)
unnamed: U1001.15 (LED8), U1003.8 (In)
unnamed: U1001.16 (LED9), U1003.7 (In)
unnamed: U1001.17 (LED10), U1003.6 (In)
unnamed: U1001.18 (LED11), U1003.5 (In)
unnamed: U1001.19 (LED12), U1003.4 (In)
unnamed: U1001.20 (LED13), U1003.3 (In)
unnamed: U1001.21 (LED14), U1003.2 (In)
unnamed: U1001.22 (LED15), U1003.1 (In)

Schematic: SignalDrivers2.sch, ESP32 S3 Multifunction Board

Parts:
C1101: .1 uf; C_0603; Mouser Part Number 710-885012206095
JP1101, JP1102, JP1103, JP1104, JP1105, JP1106, JP1107, JP1108: 0; R_1206; Mouser Part Number 71-CRCW12060000Z0EBC
P1101: C7 C6 C5 C4 C3 C2 C1 C0 C; TerminalBlock_Pheonix_MPT-2.54mm_9pol; Mouser Part Number 651-1725724
P1102: D7 D6 D5 D4 D3 D2 D1 D0 C; TerminalBlock_Pheonix_MPT-2.54mm_9pol; Mouser Part Number 651-1725724
R1101: 10K; R_0402
RP1101, RP1102: 1.5K Ohms; 4816P; Mouser Part Number 652-4816P-T1LF-1.5K
U1101: PCA9685; TSSOP-28_4.4x9.7mm_Pitch0.65mm; Mouser Part Number 771-PCA9685PW,118
U1102, U1103: TBD62X83A; SOIC-18W_7.5x11.6mm_Pitch1.27mm; Mouser Part Number 757-TBD62083AFG or 757-TBD62783AFG

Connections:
+12V: JP1101.2, JP1104.1, JP1105.2, JP1108.1; also elsewhere on the board
/MCU/SCL: U1101.26 (SCL); also elsewhere on the board
/MCU/SDA: U1101.27 (SDA); also elsewhere on the board
GND: C1101.2, JP1102.2, JP1103.1, JP1106.2, JP1107.1, U1101.2 (A1), U1101.3 (A2), U1101.4 (A3), U1101.5 (A4), U1101.14 (Vss), U1101.23 (OE), U1101.24 (A5), U1101.25 (ExtCLK); also elsewhere on the board
unnamed: JP1101.1, JP1103.2, P1101.9, U1102.10 (OC)
unnamed: JP1102.1, JP1104.2, U1102.9 (IC)
unnamed: JP1105.1, JP1107.2, P1102.9, U1103.10 (OC)
unnamed: JP1106.1, JP1108.2, U1103.9 (IC)
unnamed: P1101.1, RP1101.16 (R1.2)
unnamed: P1101.2, RP1101.15 (R2.2)
unnamed: P1101.3, RP1101.14 (R3.2)
unnamed: P1101.4, RP1101.13 (R4.2)
unnamed: P1101.5, RP1101.12 (R5.2)
unnamed: P1101.6, RP1101.11 (R6.2)
unnamed: P1101.7, RP1101.10 (R7.2)
unnamed: P1101.8, RP1101.9 (R8.2)
unnamed: P1102.1, RP1102.16 (R1.2)
unnamed: P1102.2, RP1102.15 (R2.2)
unnamed: P1102.3, RP1102.14 (R3.2)
unnamed: P1102.4, RP1102.13 (R4.2)
unnamed: P1102.5, RP1102.12 (R5.2)
unnamed: P1102.6, RP1102.11 (R6.2)
unnamed: P1102.7, RP1102.10 (R7.2)
unnamed: P1102.8, RP1102.9 (R8.2)
unnamed: R1101.1, U1101.1 (A0)
unnamed: RP1101.1 (R1.1), U1102.18 (Out)
unnamed: RP1101.2 (R2.1), U1102.17 (Out)
unnamed: RP1101.3 (R3.1), U1102.16 (Out)
unnamed: RP1101.4 (R4.1), U1102.15 (Out)
unnamed: RP1101.5 (R5.1), U1102.14 (Out)
unnamed: RP1101.6 (R6.1), U1102.13 (Out)
unnamed: RP1101.7 (R7.1), U1102.12 (Out)
unnamed: RP1101.8 (R8.1), U1102.11 (Out)
unnamed: RP1102.1 (R1.1), U1103.18 (Out)
unnamed: RP1102.2 (R2.1), U1103.17 (Out)
unnamed: RP1102.3 (R3.1), U1103.16 (Out)
unnamed: RP1102.4 (R4.1), U1103.15 (Out)
unnamed: RP1102.5 (R5.1), U1103.14 (Out)
unnamed: RP1102.6 (R6.1), U1103.13 (Out)
unnamed: RP1102.7 (R7.1), U1103.12 (Out)
unnamed: RP1102.8 (R8.1), U1103.11 (Out)
unnamed: U1101.6 (LED0), U1102.8 (In)
unnamed: U1101.7 (LED1), U1102.7 (In)
unnamed: U1101.8 (LED2), U1102.6 (In)
unnamed: U1101.9 (LED3), U1102.5 (In)
unnamed: U1101.10 (LED4), U1102.4 (In)
unnamed: U1101.11 (LED5), U1102.3 (In)
unnamed: U1101.12 (LED6), U1102.2 (In)
unnamed: U1101.13 (LED7), U1102.1 (In)
unnamed: U1101.15 (LED8), U1103.8 (In)
unnamed: U1101.16 (LED9), U1103.7 (In)
unnamed: U1101.17 (LED10), U1103.6 (In)
unnamed: U1101.18 (LED11), U1103.5 (In)
unnamed: U1101.19 (LED12), U1103.4 (In)
unnamed: U1101.20 (LED13), U1103.3 (In)
unnamed: U1101.21 (LED14), U1103.2 (In)
unnamed: U1101.22 (LED15), U1103.1 (In)

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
